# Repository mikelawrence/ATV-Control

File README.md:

# ATV Control PCB

This board was designed to act as a relay for two LED (V1 and V2) lights up to 7.5A each and a horn (H) up to 20A. Each LED Output has a control switch input and indicator LED output. When the Ignition input is on (12V) indicates the ATV is running so the Reverse input will turn LED V2 output on when at 12V and the High Beam input will turn LED V1 output on when at 12V. Turning Ignition off (0V) will turn off all LED outptus (V1 and V2). The control switches allows manual control the LED lights even when the ATV off. When you turn a LED on with a control switch the LED light will remain on for a configurable amount of time (1-20 minutes). This delay off will prevent the battery from being discharged.

The horn is controlled by a switch just like the LED outputs but it has three indicator LEDs (Red, Green, and Blue). When the horn control switch is pressed any currently on LED outputs (V1 or V2) will be turned off to reduce overall current throught the board. The horn will not work if Ignition is not on (12V).

## Status and Testing

* Rev 1.0 has been ordered and tested.
  * You can order parts from Mouser using this [shared BOM](https://www.mouser.com/ProjectManager/ProjectDetail.aspx?AccessID=3e10d07292).
  * You can order the PCB from [OSH Park](https://oshpark.com/shared_projects/YVj5Y8EP).

## Board Preview

## Notes

* This board must have a 20A fuse or other safety device on the input.
* The Reverse Input is configured for my 2020 Yamaha Grizzly 700. The reverse switch is connected to ground when ATV is in reverse, otherwise it is pulled up to 12V by the Engine Control Unit. R17 is used to pulldown this input to prevent a floating input from causing problems. However this pulldown is a high enough impedance to not affect the pullup in the Engine Control Unit. You will need to adjust this input to match your specific ATV.
* The board's current usage is about than 0.25 mA when idle. This represents a small but never the less non-zero current draw on the ATV's battery even when the ignition is off. My ATV is used frequently so this is not an issue but if you plan on storing the ATV long term you should be using a trickle charger to keep the battery topped off. Or pull that 20 A fuse you added to the 12V input to this PCB.
* I used High-Side switch from Infineon for all the high current outputs. These chips are designed for automotive environments to drive resistive, capacitive, and inductive loads while providing over current, over temperature, over voltage, and reverse polarity protections. I also used these High-Side Switches for the indicator LEDs even though it is a bit overkill.
* The Horn circuit is a relatively high current at 20A. There is missing solder mask on the bottom of the PCB. It is expected that additional solder will be placed on this section to improve current handling. You should also plan on adding a 16 AWG wire between the GND input and the H- connections.
* This PCB design expects 2 oz copper for both sides.
* Assembling this PCB will require a reflow oven or hot air. [Whizoo](http://www.whizoo.com/) sells a nice kit to make your own reflow oven.
* This PCB design uses my custom libraries available here [Mike's KiCad Libraries](https://github.com/mikelawrence/KiCad-Libraries).
* PCB is designed in [KiCad](http://kicad-pcb.org) which is a great free EDA toolset.
* For Bill of Materials generation I use my version of [KiBoM](https://github.com/mikelawrence/KiBoM) forked from [SchrodingersGat](https://github.com/SchrodingersGat/KiBoM).

## Software

The microcontroller is a Atmel/Microchip XMega8E5. Software is written in C using the free [Microchip Studio for AVR](https://www.microchip.com/mplab/microchip-studio) free cross compiler and development environment. My normal AVR debugging tool is [Atmel-ICE](https://www.microchip.com/DevelopmentTools/ProductDetails/atatmel-ice). You can get it for as low as $62 in the form of a board from Digikey or Mouser. Instead of the standard programming header I use the Tag-Connect cable and it's space saving [footprint](https://www.tag-connect.com/product/tc2030-nl-fp-footprint). [This](https://www.tag-connect.com/product/tc2030-icespi-nl-no-leg-cable-for-use-with-atmel-ice) is Tag-Connect cable I use with the Atmel-ICE.

## Board Installation

I use Sugru moldable silicone to encapsulate this PCB to prevent water damage.

## End Result

The push button switches were installed in the center headlight cluster. Looking from the front the center pushbutton is the horn. The two push buttons on the right control the LED lights. The two buttons on the left are buttons for the Homelink controller ([60-HMLKV5BLK](https://www.amazon.com/gp/product/B00A79G9FY/ref=ppx_yo_dt_b_search_asin_title?ie=UTF8&psc=1)) so I can control my front gate and one garage door. This is not part of the ATV Control PCB.

For the front of the ATV I installed a Black Oak [10" Dual Row, 100W Flood LED Light Bar](https://www.blackoakled.com/collections/double-row-led/products/10-two-row-led-light-bar-combination-beam-pattern-white-osram) and two Black Oak [2" Single Row, 20W Scene LED Light Bars](https://www.blackoakled.com/products/new-2-inch-single-row-series-led-light-bar-with-scene-optics?_pos=6&_sid=0f2b0b32f&_ss=r). All three LED Light Bars draw just under 7 A which is just below the maximum current of 7.5 A for that output. I used Axia Alloy mounts for the LED Light Bars. They are expensive but look good and are strong at the same time. The front rack on the 2020 Grizzly is 7/8" in diameter.

I added a Black Oak [2" 40W Diffused LED Pod Light](https://www.blackoakled.com/products/new-2-inch-diffused-pod-light-powerful-turret-style-pod-40w-cree-xm-l2?_pos=1&_sid=a00cf89ab&_ss=r) to the rear of the ATV mainly as a backup light. This LED Light draws 4.1 A which is just fine for the LED outputs. The accessory brush guard has a nice mounting point for this light right in the middle and well protected.

Here is a picture taken at night just after dusk. This is the front shot with all three light bars on. The fence line is 200 ft away and the shot is from behind the ATV. The slightly different color temperature on the left and right shows how the small light bars increase the visiblity on the sides. I'm happy with the results.

This the rear shot again slightly after dusk with the rear pointed at the same fence line but about 25 ft away. The diffuse optics make the light more even, less sharp. It probably decreases the overall light output for a more pleasing distrubution. You loose distance for more even coverage.

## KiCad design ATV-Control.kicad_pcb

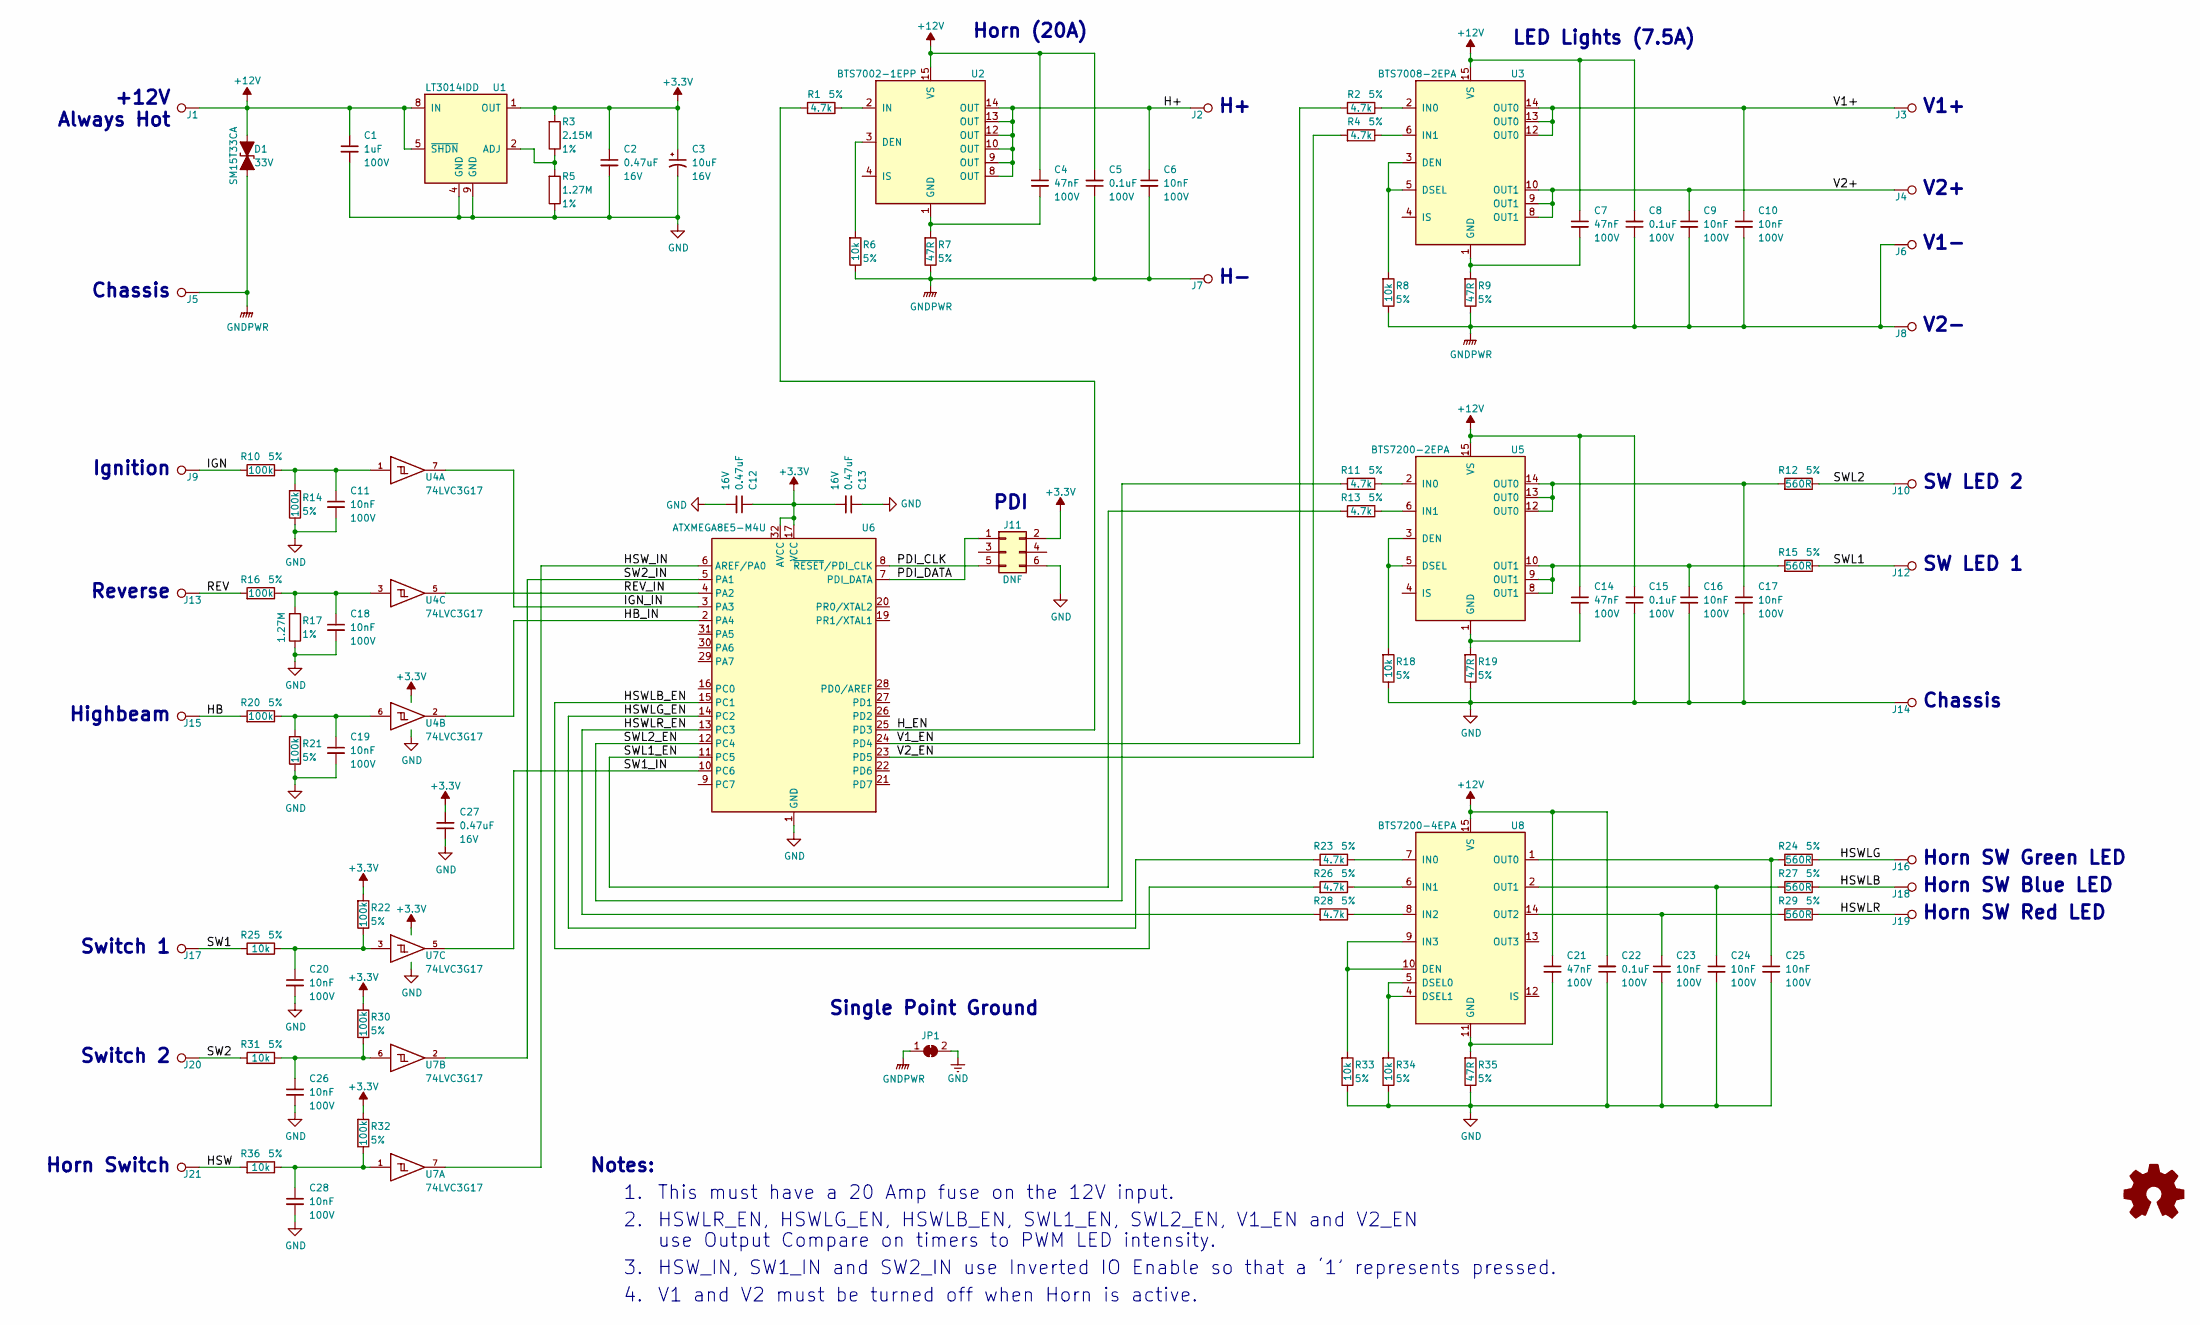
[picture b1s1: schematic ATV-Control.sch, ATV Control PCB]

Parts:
C1: 1uF; C_0805_2012Metric; Voltage 100V; Part Number GRJ21BC72A105KE11L
C2, C12, C13, C27: 0.47uF; C_0603_1608Metric; Voltage 16V; Part Number GRM188R71C474KA88
C3: 10uF; CP_EIA-3216-18_Kemet-A; Tolerance 20%; Voltage 16V; Part Number T491A106M016AT7280
C4, C7, C14, C21: 47nF; C_0603_1608Metric; Voltage 100V; Part Number GCJ188R92A473KA1D
C5, C8, C15, C22: 0.1uF; C_0603_1608Metric; Voltage 100V; Part Number GCJ188R72A104KA1D
C6, C9, C10, C11, C16, C17, C18, C19, C20, C23, C24, C25, C26, C28: 10nF; C_0603_1608Metric; Voltage 100V; Part Number GCM188R72A103KA7D
D1: SM15T33CA; D_SMC_Handsoldering; Voltage 33V; Part Number SM15T33CA
J1, J2, J3, J4, J5, J6, J7, J8: TEST_1P; SolderWire-1x01_D2mm_OD3.81mm
J9, J10, J12, J13, J14, J15, J16, J17, J18, J19, J20, J21: TEST_1P; SolderWire-1x01_D1mm_OD2.54mm
J11: DNF; TC2030-IDC-NP; Part Number TC2030-ICESPI-NL
JP1: Jumper; SolderJumper-2_P1.3mm_Bridged2Bar_Pad1.0x1.5mm
R1, R2, R4, R11, R13, R23, R26, R28: 4.7k; R_0603_1608Metric; Tolerance 5%; Part Number RC0603JR-074K7L
R3: 2.15M; R_0603_1608Metric; Tolerance 1%; Part Number CRCW06032M15FKEA
R5, R17: 1.27M; R_0603_1608Metric; Tolerance 1%; Part Number CRCW06031M27FKEA
R6, R8, R18, R25, R31, R33, R34, R36: 10k; R_0603_1608Metric; Tolerance 5%; Part Number RC0603JR-0710KL
R7, R9, R19, R35: 47R; R_0603_1608Metric; Tolerance 5%; Part Number RC0603FR-0747RL
R10, R14, R16, R20, R21, R22, R30, R32: 100k; R_0603_1608Metric; Tolerance 5%; Part Number RC0603JR-07100KL
R12, R15, R24, R27, R29: 560R; R_1206_3216Metric; Tolerance 5%; Part Number ERJ-8GEYJ561V
U1: LT3014IDD; DFN-8-1EP_3x3mm_P0.5mm_EP1.66x2.38mm; Part Number LT3014BHVIDD#PBF
U2: BTS7002-1EPP; Infineon_PG-TSDSO-14-22; Part Number BTS70021EPPXUMA1
U3: BTS7008-2EPA; Infineon_PG-TSDSO-14-22; Part Number BTS70082EPAXUMA1
U4, U7: 74LVC3G17; VSSOP-8_2.3x2mm_P0.5mm; Part Number SN74LVC3G17DCUR
U5: BTS7200-2EPA; Infineon_PG-TSDSO-14-22; Part Number BTS72002EPAXUMA1
U6: ATXMEGA8E5-M4U; QFN-32-1EP_4x4mm_P0.4mm_EP2.65x2.65mm; Part Number ATXMEGA8E5-M4U
U8: BTS7200-4EPA; Infineon_PG-TSDSO-14-22; Part Number BTS72004EPAXUMA1

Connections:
+3.3V: C2.1, C3.1, C12.1, C13.2, C27.2, J11.2, R3.2, R22.2, R30.2, R32.2, U1.1 (OUT), U4.8 (VCC), U6.17 (VCC), U6.32 (AVCC), U7.8 (VCC)
+12V: C1.1, C4.1, C5.2, C7.1, C8.2, C14.1, C15.2, C21.1, C22.2, D1.1 (A1), J1.1, U1.5 (~SHDN), U1.8 (IN), U2.15 (VS), U3.15 (VS), U5.15 (VS), U8.15 (VS)
/H+: C6.1, J2.1, U2.8 (OUT), U2.9 (OUT), U2.10 (OUT), U2.12 (OUT), U2.13 (OUT), U2.14 (OUT)
/HB: J15.1, R20.2
/HB_IN: U4.2, U6.2 (PA4)
/HSW: J21.1, R36.2
/HSWLB: J18.1, R27.1
/HSWLB_EN: R26.2, U6.15 (PC1)
/HSWLG: J16.1, R24.1
/HSWLG_EN: R23.2, U6.14 (PC2)
/HSWLR: J19.1, R29.1
/HSWLR_EN: R28.2, U6.13 (PC3)
/HSW_IN: U6.6 (AREF/PA0), U7.7
/H_EN: R1.2, U6.25 (PD3)
/IGN: J9.1, R10.2
/IGN_IN: U4.7, U6.3 (PA3)
/PDI_CLK: J11.5, U6.8 (~RESET~/PDI_CLK)
/PDI_DATA: J11.1, U6.7 (PDI_DATA)
/REV: J13.1, R16.2
/REV_IN: U4.5, U6.4 (PA2)
/SW1: J17.1, R25.2
/SW1_IN: U6.10 (PC6), U7.5
/SW2: J20.1, R31.2
/SW2_IN: U6.5 (PA1), U7.2
/SWL1: J12.1, R15.1
/SWL1_EN: R13.2, U6.11 (PC5)
/SWL2: J10.1, R12.1
/SWL2_EN: R11.2, U6.12 (PC4)
/V1+: C10.1, J3.1, U3.12 (OUT0), U3.13 (OUT0), U3.14 (OUT0)
/V1_EN: R2.2, U6.24 (PD4)
/V2+: C9.1, J4.1, U3.8 (OUT1), U3.9 (OUT1), U3.10 (OUT1)
/V2_EN: R4.2, U6.23 (PD5)
GND: C1.2, C2.2, C3.2, C11.2, C12.2, C13.1, C15.1, C16.2, C17.2, C18.2, C19.2, C20.2, C22.1, C23.2, C24.2, C25.2, C26.2, C27.1, C28.2, J11.6, J14.1, JP1.2 (B), R5.1, R14.1, R17.1, R18.1, R19.1, R21.1, R33.1, R34.1, R35.1, U1.4 (GND), U1.9 (GND), U4.4 (GND), U6.1 (GND), U6.18 (GND), U6.33 (GND), U7.4 (GND)
GNDPWR: C5.1, C6.2, C8.1, C9.2, C10.2, D1.2 (A2), J5.1, J6.1, J7.1, J8.1, JP1.1 (A), R6.1, R7.1, R8.1, R9.1
unnamed: C4.2, R7.2, U2.1 (GND)
unnamed: C7.2, R9.2, U3.1 (GND)
unnamed: C11.1, R10.1, R14.2, U4.1
unnamed: C14.2, R19.2, U5.1 (GND)
unnamed: C16.1, R15.2, U5.8 (OUT1), U5.9 (OUT1), U5.10 (OUT1)
unnamed: C17.1, R12.2, U5.12 (OUT0), U5.13 (OUT0), U5.14 (OUT0)
unnamed: C18.1, R16.1, R17.2, U4.3
unnamed: C19.1, R20.1, R21.2, U4.6
unnamed: C20.1, R22.1, R25.1, U7.3
unnamed: C21.2, R35.2, U8.11 (GND)
unnamed: C23.1, R29.2, U8.14 (OUT2)
unnamed: C24.1, R27.2, U8.2 (OUT1)
unnamed: C25.1, R24.2, U8.1 (OUT0)
unnamed: C26.1, R30.1, R31.1, U7.6
unnamed: C28.1, R32.1, R36.1, U7.1
unnamed: R1.1, U2.2 (IN)
unnamed: R2.1, U3.2 (IN0)
unnamed: R3.1, R5.2, U1.2 (ADJ)
unnamed: R4.1, U3.6 (IN1)
unnamed: R6.2, U2.3 (DEN)
unnamed: R8.2, U3.3 (DEN), U3.5 (DSEL)
unnamed: R11.1, U5.2 (IN0)
unnamed: R13.1, U5.6 (IN1)
unnamed: R18.2, U5.3 (DEN), U5.5 (DSEL)
unnamed: R23.1, U8.7 (IN0)
unnamed: R26.1, U8.6 (IN1)
unnamed: R28.1, U8.8 (IN2)
unnamed: R33.2, U8.9 (IN3), U8.10 (DEN)
unnamed: R34.2, U8.4 (DSEL1), U8.5 (DSEL0)

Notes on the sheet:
PDI
Highbeam
Ignition
Reverse
V2-
V1-
V2+
V1+
+12V Always Hot
SW LED 1
SW LED 2
Chassis
Horn SW Red LED
Horn SW Green LED
Horn SW Blue LED
Horn Switch
Switch 1
Switch 2
Single Point Ground
Horn (20A)
LED Lights (7.5A)
Notes:
HSWLR_EN, HSWLG_EN, HSWLB_EN, SWL1_EN, SWL2_EN, V1_EN and V2_EN
use Output Compare on timers to PWM LED intensity.
HSW_IN, SW1_IN and SW2_IN use Inverted IO Enable so that a ‘1’ represents pressed.
V1 and V2 must be turned off when Horn is active.
This must have a 20 Amp fuse on the 12V input.

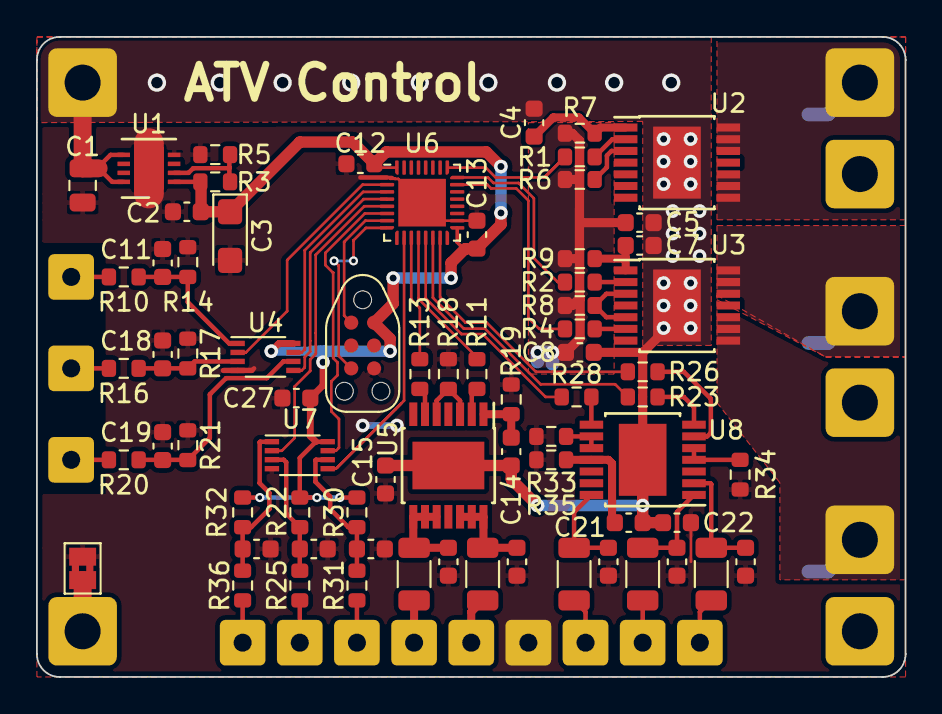
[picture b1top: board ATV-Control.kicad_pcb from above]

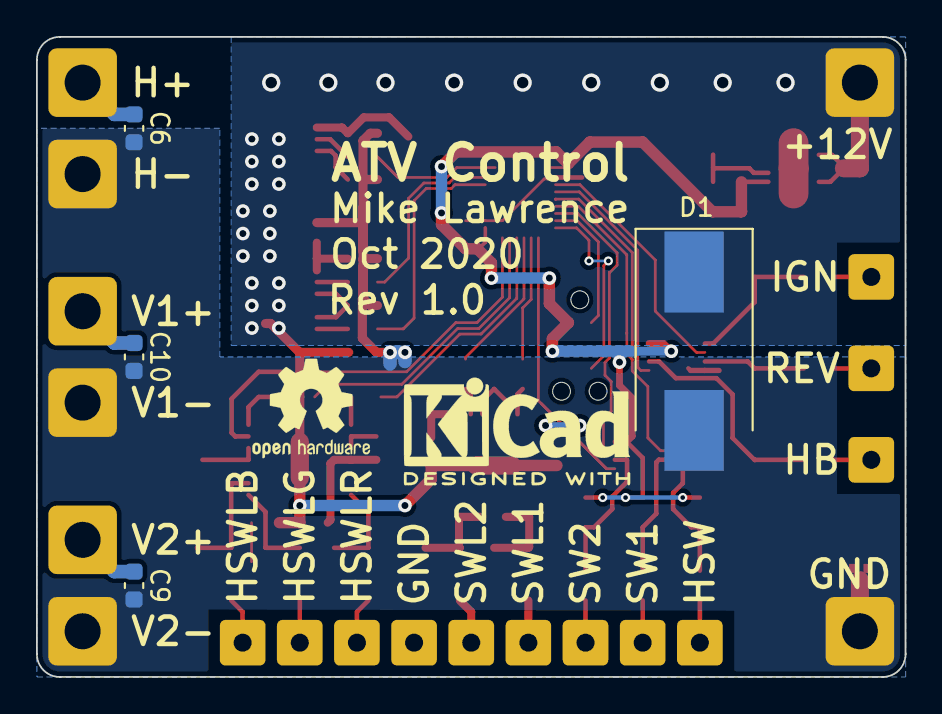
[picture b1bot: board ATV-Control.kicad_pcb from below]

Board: 2 copper layers, 48.3 x 35.6 mm, 95 parts (4 on the bottom side), 63 nets.

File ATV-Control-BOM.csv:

Quantity,References,Value,Description,Manufacturer,Part Number,Vendor,Vendor Part Number
1,C1,1uF,"CAP, 0805, 1uF, 10%, X7S, 100V",Murata Electronics,GRJ21BC72A105KE11L,Mouser,81-GRJ21BC72A105KE1L
4,C2 C12 C13 C27,0.47uF,"CAP, 0603, 0.47uF, 10%, X7R, 16V",Murata Electronics,GRM188R71C474KA88,Mouser,81-GRM188R71C474KA88
1,C3,10uF,"CAP, A Size, 10uF, 20%, Tantalum, 16V",Kemet,T491A106M016AT7280,Mouser,80-T491A106M016AT7280
4,C4 C7 C14 C21,47nF,"CAP, 0603, 47nF, 10%, X8R, 100V",Murata Electronics,GCJ188R92A473KA1D,Mouser,81-GCJ188R92A473KA1D
4,C5 C8 C15 C22,0.1uF,"CAP, 0603, 0.1uF, 10%, X8R, 100V",Murata Electronics,GCJ188R72A104KA1D,Mouser,81-GCJ188R72A104KA1D
14,C6 C9 C10 C11 C16 C17 C18 C19 C20 C23 C24 C25 C26 C28,10nF,"CAP, 0603, 10nF, 10%, X7R, 100V",Murata Electronics,GCM188R72A103KA7D,Mouser,81-GCM188R72A103KA7D
1,D1,SM15T33CA,"TVS, SMC, Bi-directional, 1500W",ST,SM15T33CA,Mouser,511-SM15T33CA
8,R1 R2 R4 R11 R13 R23 R26 R28,4.7k,"RES, 0603, 4.7k, 1/10W, 5%, T100",Yageo,RC0603JR-074K7L,Mouser,603-RC0603JR-074K7L
1,R3,2.15M,"RES, 0603, 2.15M, 1/10W, 1%, T100",Vishay,CRCW06032M15FKEA,Mouser,71-CRCW06032M15FKEA
2,R5 R17,1.27M,"RES, 0603, 1.27M, 1/10W, 1%, T100",Vishay,CRCW06031M27FKEA,Mouser,71-CRCW06031M27FKEA
8,R6 R8 R18 R25 R31 R33 R34 R36,10k,"RES, 0603, 10k, 1/10W, 5%, T100",Yageo,RC0603JR-0710KL,Mouser,603-RC0603JR-0710KL
4,R7 R9 R19 R35,47R,"RES, 0603, 47R, 1/10W, 5%, T100",Yageo,RC0603FR-0747RL,Mouser,603-RC0603FR-0747RL
8,R10 R14 R16 R20 R21 R22 R30 R32,100k,"RES, 0603, 100k, 1/10W, 5%, T100",Yageo,RC0603JR-07100KL,Mouser,603-RC0603JR-07100KL
5,R12 R15 R24 R27 R29,560R,"RES, 1206, 560R, 1/2W, 5%, T200",Panasonic,ERJ-8GEYJ561V,Mouser,667-ERJ-8GEYJ561V
1,U1,LT3014IDD,"IC, DFN-8, Linear Regulator, LDO, 80V, 20mA",Linear Tech,LT3014BHVIDD#PBF,Mouser,584-LT3014BHVIDD#PBF
1,U2,BTS7002-1EPP,"IC, TSDSO-14, High-Side Switch, Single, 21A",Infineon,BTS70021EPPXUMA1,Mouser,726-BTS70021EPPXUMA1
1,U3,BTS7008-2EPA,"IC, TSDSO-14, High-Side Switch, Dual, 7.5A",Infineon,BTS70082EPAXUMA1,Mouser,726-BTS70082EPAXUMA1
2,U4 U7,74LVC3G17,"IC, VSSOP-8, Triple Schmitt-Trigger Buffer",TI,SN74LVC3G17DCUR,Mouser,595-SN74LVC3G17DCUR
1,U5,BTS7200-2EPA,"IC, TSDSO-14, High-Side Switch, Dual, 1.2A",Infineon,BTS72002EPAXUMA1,Mouser,726-BTS72002EPAXUMA1
1,U6,ATXMEGA8E5-M4U,"IC, QFN-32, 8/16-bit AVR XMEGA Microcontroller, 8kB",Atmel,ATXMEGA8E5-M4U,Mouser,556-ATXMEGA8E5-M4U
1,U8,BTS7200-4EPA,"IC, TSDSO-14, High-Side Switch, Quad, 1A",Infineon,BTS72004EPAXUMA1,Mouser,726-BTS72004EPAXUMA1

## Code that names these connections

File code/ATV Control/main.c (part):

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#define SWL2EN_port						PORTC
#define SWL2EN_bp						PIN4_bp
// Input defines
#define IGN_port						PORTA
#define IGN_bp							PIN3_bp
#define REV_port						PORTA
#define REV_bp							PIN2_bp
#define HB_port							PORTA
#define HB_bp							PIN4_bp
#define HSW_port						PORTA
#define HSW_bp							PIN0_bp
#define SW2_port						PORTA
#define SW2_bp							PIN1_bp
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 */
void v12_off(void)
{
	TCD5.CCABUF = 0;									// OC5A set to 0% duty cycle (V1_EN)
	TCD5.CCBBUF = 0;									// OC5B set to 0% duty cycle (V2_EN)
	TCD5.CTRLGSET = TC_CMD_UPDATE_gc;					// Force TCD5 timer UPDATE
}

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 */
void v1_off(void)
{
	TCD5.CCABUF = 0;									// OC5A set to 0% duty cycle (V1_EN)
}

/* 
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 */
void v2_off(void)
{
	TCD5.CCBBUF = 0;									// OC5B set to 100% duty cycle (V2_EN)
}

/* 
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			PORTR.PIN0CTRL = PORT_OPC_PULLDOWN_gc;		// PORTR is all pull-downs
			// Configure IGN input
			PORTCFG.MPCMASK = (1 << IGN_bp);			// Multi-Pin Configuration select input
			IGN_port.PIN0CTRL = PORT_OPC_TOTEM_gc		// Input is not pulled down
			                  | PORT_ISC_BOTHEDGES_gc;	// Input interrupt on any edge
			IGN_port.INTCTRL = PORT_INTLVL_HI_gc;		// Interrupt will be high level
			IGN_port.INTMASK |= (1 << IGN_bp);			// Input interrupt enabled
			// Configure REV input
			PORTCFG.MPCMASK = (1 << REV_bp);			// Multi-Pin Configuration select input
			REV_port.PIN0CTRL = PORT_OPC_TOTEM_gc		// Input is not pulled down
			                  | PORT_ISC_BOTHEDGES_gc;	// Input interrupt on any edge
			REV_port.INTCTRL = PORT_INTLVL_HI_gc;		// Interrupt will be high level
			REV_port.INTMASK |= (1 << REV_bp);			// Input interrupt enabled
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			HB_port.INTMASK |= (1 << HB_bp);			// Input interrupt enabled
			// Configure HSW input
			PORTCFG.MPCMASK = (1 << HSW_bp);			// Multi-Pin Configuration select input
			HSW_port.PIN0CTRL = PORT_OPC_TOTEM_gc		// Input is not pulled down
			                  | PORT_ISC_BOTHEDGES_gc	// Input interrupt on any edge
							  | (1 << PORT_INVEN_bp);	// Invert this input
			HSW_port.INTCTRL = PORT_INTLVL_HI_gc;		// Interrupt will be high level
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
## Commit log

2020-11-22 Update board images.
2020-11-22 Update README.
2020-11-22 Add pictures of the ATV and updated the README.
2020-11-22 Update board images
2020-11-22 Remove depreciated code elements. Update README.
2020-11-23 Add night time pictures.
